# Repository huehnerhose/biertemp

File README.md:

biertemp
========

Atmega Project for automated temperature and timecontrol

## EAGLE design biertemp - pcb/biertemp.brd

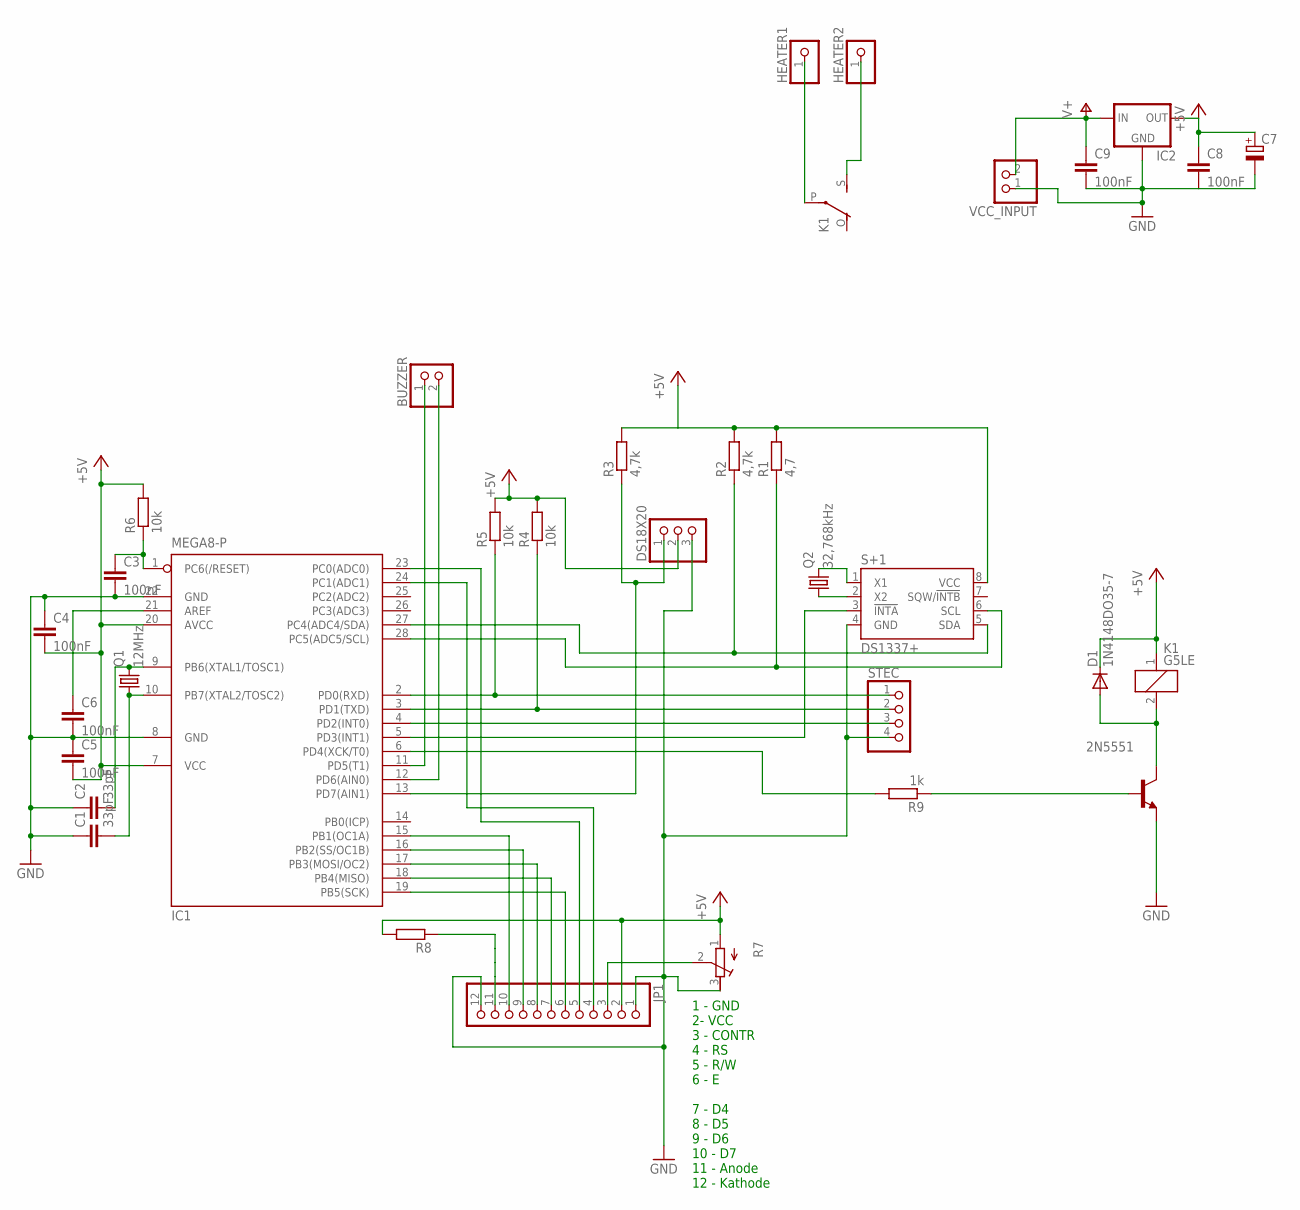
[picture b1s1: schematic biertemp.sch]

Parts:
2N5551: -NPN-TO92-EBC; TO92-EBC
BUZZER: PINHD-1X2; 1X02
C1, C2: 33pF; C025-024X044
C3, C4, C5, C6, C8, C9: 100nF; C025-024X044
C7: CPOL-EUE5-8.5; E5-8,5
D1: 1N4148DO35-7; DO35-7
DS18X20: PINHD-1X3; 1X03
HEATER1, HEATER2: PINHD-1X1; 1X01
IC1: MEGA8-P; DIL28-3
IC2: 78XXS
JP1: PINHD-1X12; 1X12
K1: G5LE
Q1: 12MHz; HC49/S
Q2: 32,768kHz; TC26V
R1: 4,7; 0204/7
R2, R3: 4,7k; 0204/7
R4, R5, R6: 10k; 0204/7
R7: R-TRIMM64X; RTRIM64X
R8: R-EU_0204/7; 0204/7
R9: 1k; 0204/7
S+1: DS1337+; DIL8
STEC: PINHD-1X4; 1X04
VCC_INPUT: PINHD-1X2; 1X02

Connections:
+5V: C4.2, C5.2, C7.+, C8.1, D1.C, DS18X20.2, IC1.7 (VCC), IC1.20 (AVCC), IC2.OUT, JP1.2, K1.1, R1.2, R2.2, R3.2, R4.2, R5.2, R6.2, R7.1 (A), R8.2, S+1.8 (VCC)
GND: 2N5551.E, C1.1, C2.1, C3.2, C4.1, C5.1, C6.2, C7.-, C8.2, C9.2, DS18X20.3, IC1.8 (GND), IC1.22 (GND), IC2.GND, JP1.1, JP1.12, R7.3 (E), S+1.4 (GND), STEC.4, VCC_INPUT.1
unnamed: IC1.4 (PD2(INT0)), STEC.3
unnamed: DS18X20.1, IC1.13 (PD7(AIN1)), R3.1
unnamed: C6.1, IC1.21 (AREF)
unnamed: Q2.1, S+1.2 (X2)
unnamed: C3.1, IC1.1 (PC6(/RESET)), R6.1
unnamed: C2.2, IC1.9 (PB6(XTAL1/TOSC1)), Q1.2
unnamed: C1.2, IC1.10 (PB7(XTAL2/TOSC2)), Q1.1
unnamed: IC1.6 (PD4(XCK/T0)), R9.2
unnamed: IC1.3 (PD1(TXD)), R4.1, STEC.2
unnamed: Q2.2, S+1.1 (X1)
unnamed: IC1.5 (PD3(INT1)), S+1.3 (!INTA)
unnamed: IC1.27 (PC4(ADC4/SDA)), R2.1, S+1.5 (SDA)
unnamed: IC1.28 (PC5(ADC5/SCL)), R1.1, S+1.6 (SCL)
unnamed: IC1.15 (PB1(OC1A)), JP1.10
unnamed: JP1.11, R8.1
unnamed: JP1.3, R7.2 (S)
unnamed: IC1.16 (PB2(SS/OC1B)), JP1.9
unnamed: IC1.17 (PB3(MOSI/OC2)), JP1.8
unnamed: IC1.18 (PB4(MISO)), JP1.7
unnamed: IC1.19 (PB5(SCK)), JP1.6
unnamed: IC1.23 (PC0(ADC0)), JP1.5
unnamed: IC1.24 (PC1(ADC1)), JP1.4
unnamed: BUZZER.1, IC1.11 (PD5(T1))
unnamed: IC1.2 (PD0(RXD)), R5.1, STEC.1
unnamed: BUZZER.2, IC1.12 (PD6(AIN0))
unnamed: 2N5551.B, R9.1
unnamed: 2N5551.C, D1.A, K1.2
unnamed: HEATER1.1, K1.P
unnamed: HEATER2.1, K1.S
V+: C9.1, IC2.IN, VCC_INPUT.2

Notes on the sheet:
1 - GND 2- VCC 3 - CONTR 4 - RS 5 - R/W 6 - E 7 - D4 8 - D5 9 - D6 10 - D7 11 - Anode 12 - Kathode

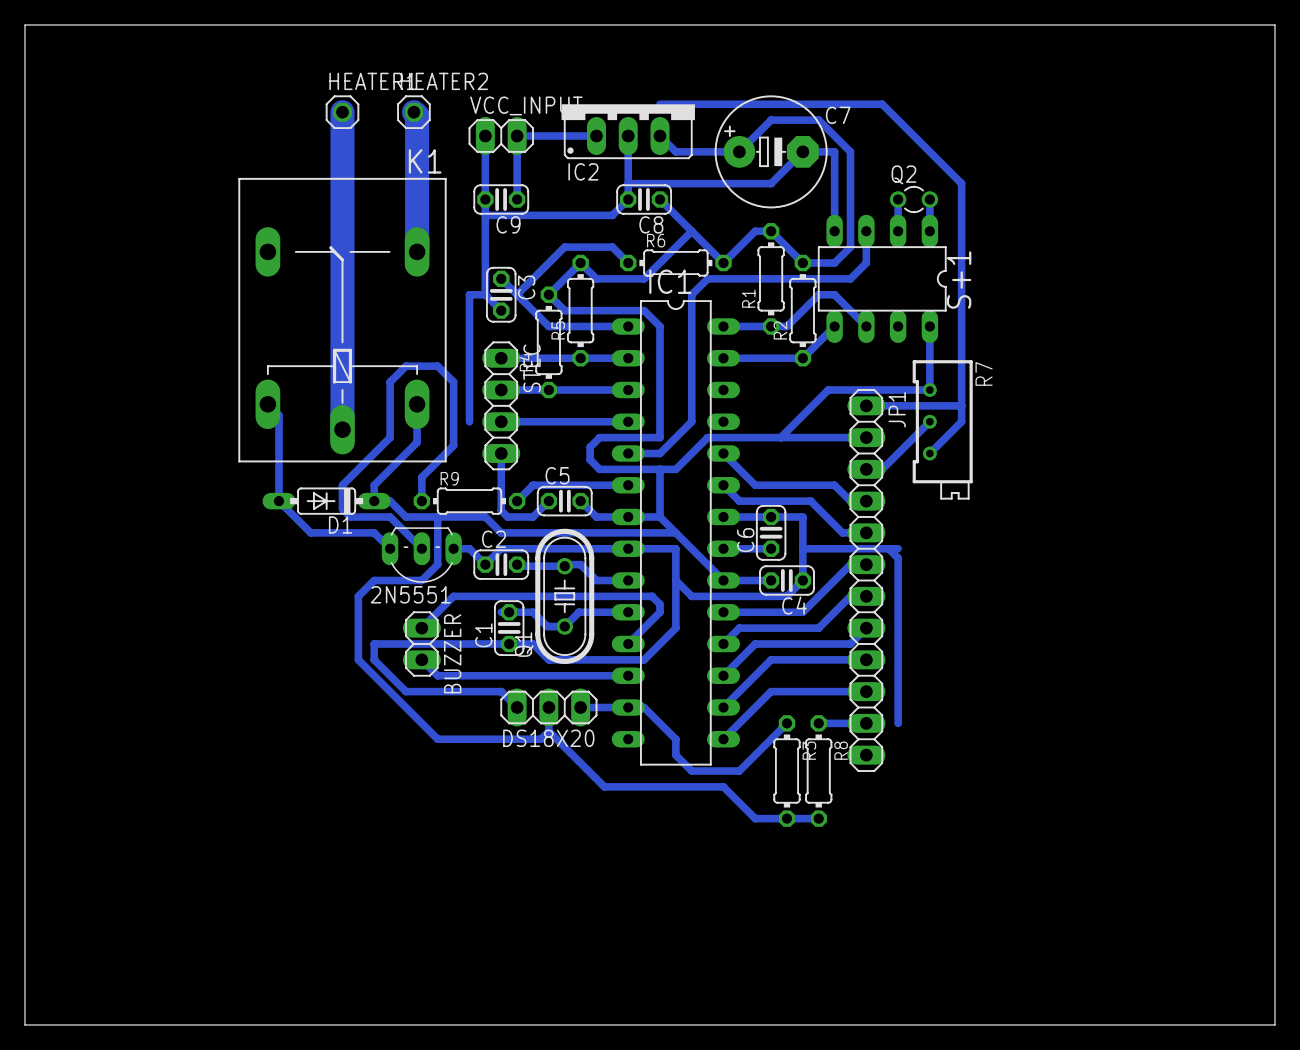
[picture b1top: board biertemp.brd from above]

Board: 2 copper layers, 100.0 x 80.0 mm, 33 parts (0 on the bottom side), 32 nets.

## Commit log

2013-12-02 DS1337 Code ausgelagter frontend Code - "ELSE" DebugRoutine verändert, Flags ausgeweitet, ALARM vorbereitet
2013-12-04 just some comments
2013-12-04 modularize debounce
2013-12-04 modularize and rename
2013-12-04 many comments added modularization finished - testing pending
2013-12-04 tested and working
2013-12-04 frontend completed set temperature range set timer
2013-12-05 minor code changes
    Added first PCB Draft
2013-12-06 FIX: Set DDRC PC2&3 explicit input!
2013-12-06 added acoustic noise generation for timer
2013-12-06 ADD: Auto timer stop if measMiddle < rangeMin. Now Timer only runs if temperature is in range ADD: DEBUG_CLOCK --> Changes Mainview ADD: ds1337_startClock and ds1337_stopClock -> starts/stops clock (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
2013-12-06 ADD: Heater switch / logic
2013-12-06 UPDATE: Schematics now including heater and buzzer
2013-12-06 want to merge branches
2013-12-07 first pcb version finished, including pcb design changed ports for better layout NEW: All port definitions now with macros
2013-12-08 FIX: definition / declaration of Flag type and definition of Flags variable
2013-12-08 UPDATE: changed PCB Layout
2013-12-11 PCB Update
2013-12-11 clean up repository
2015-02-18 switched to Makefile compilation

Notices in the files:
parts and their libraries:
eagle-library-edeca.net-v5: This is v1 and is licensed under the Creative Commons (Attribution-Non-Commercial-Share Alike 2.0 UK)
